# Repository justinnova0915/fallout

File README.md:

# TALOS-01 // Desktop Helper

The TALOS-01 is a desktop device designed to make navigating workspace-heavy, tiling operating systems (like Arch Linux Hyprland or macOS) more straightforward by making it physical. No more memorizing convoluted keyboard shortcuts just to move a window. This is my Fallout project for Hack Club, so I'm super excited to share it!

## Why TALOS-01?

Tiling window managers like Hyprland are great, but relying entirely on abstract keybinds can get annoying and lacks physical intuition. The goal of TALOS-01 is to turn window and workspace management into a tactile experience.

## Custom Features

- The device splits into a Main Console and a Macro Pad that snap together using strong magnet pogo pins.
- The device uses an MGN7H miniature linear rail with a button on it to let you grab and slide windows across active workspaces.
- Dedicated DMG19480T088_01WN screen displays useful widgets (time, weather, Discord call status) to free up your main monitor real estate entirely for games or code.
- A custom 3x3 macro pad module for standard macro inputs.
- A physical 5V analog needle voltmeter to display real-time metrics like CPU usage or core temperatures.
- Powerful ESP32 Controller for the brain of the device. Communicates with your PC over Bluetooth.
- Supports wireless power using two internal 18650 batteries, or wired over USB-C.

## Device Design

The TALOS-01 design is heavily inspired by the design language of *Arknights: Endfield*. The entire body uses a matching color palette of black, grey, white, and yellow, detailed with topographic lines and techy text accents.

> Disclaimer: This project is a non-commercial, fan-made creation featuring visual and UI assets inspired by *Arknights: Endfield*, which remain the intellectual property of **Hypergryph**.

* **PCB and circuitry:**
It's built around a custom parent PCB that hosts every single chip. The board has exposed headers to connect to the moving slider handle and the macro pad (excuse any messy routing) ;).  
To power it, you can plug in USB-C to feed the TP4056 charging circuit, or let it run completely wireless off the 18650 batteries. Power leaving the circuit is stepped up using two independent MT3608 boost converters (a 12V line for the smart display and a 5V line for the ESP32 and voltmeter), before hitting an AMS1117-3.3 linear regulator for the shared sensor bus.

* **The Slider & Encoder:** The custom 3D-printed handle rides on the MGN7H rail and holds a DRV2605 driver with a motor to deliver physical haptic feedback clicks as you pass items. Distance tracking is calculated using two SS49E hall effect sensors positioned exactly a quarter turn from each other on the bottom of the block. All sensors and drivers tucked inside the moving handle connect back to the parent PCB via a Flat Flexible Cable (FFC).

* **Macro Pad:** To avoid a massive, fragile bundle of wires across the split-enclosure gap, I put a PCF8574 IO expander to condense the 3x3 matrix, gauge, and power button down into a simple 4-line I2C bus, meaning the whole wing connection only needs 7 physical pogo pins to bridge the gap! The analog needle gauge runs on a 5V scale, but the ESP32 can only natively supply a 3.3V logic signal. I put together a simple 2N3094 transistor circuit to shift the downstream signal up cleanly to the required 5V.

## Firmware and Software
The screen graphics are built and flashed to the hardware independently using DWIN's native configuration environment and software utility tools. This allows the smart display to handle its own graphics processing over an 8-pin connection to the ESP32. This stops the ESP32 from lagging out under heavy rendering, so it can focus purely on passing lightweight UI control commands over UART!

On the desktop side, a custom-written daemon in GOLANG runs continuously to translate signals coming from the ESP32 over Bluetooth and send information to the device.

## How to Build and Use

#### 1. Hardware Assembly
1. **PCB:** Get the board fabricated using the gerbers files inside `Fallout_PCB`.
2. **Components:** Grab all components listed in the [BOM](https://github.com/justinnova0915/fallout/blob/main/BOM.csv).
3. **3D Printing & Assembly:** Print the housing from `Fallout_CAD`, and assemble according to the 3d model.
4. **Wiring Diagram**  
  
Wiring diagram for the main board  
  
Macro Pad Wiring Diagram
#### 2. Flashing Firmware
- **Smart Display:** The screen graphics are built and flashed to the hardware independently using DWIN's native configuration environment and software utility tools call DGUS. Simply follow their Bilibili tutorial.
- **ESP32 Core:** Open the `Fallout_Software/Firmware` project in your environment, then build and flash using vscode's esp-idf tool.

#### 3. Desktop Software Setup
The desktop side uses a custom daemon written in `GO` that runs continuously to catch Bluetooth strings from the ESP32 and talk to your window manager.
1. Move into the daemon directory:
    ```bash
    cd Fallout_Software/Daemon
    ```
2. Build the binary:
    ```bash
    go build main.go
    ```
3. Boot it on startup by adding it to your `hyprland.conf`:
    ```ini
    exec-once = /path/to/talos-daemon
    ```

## Resources

#### BOM
I got most of my components in person in China, but I have found equivalents for around the same price on Taobao, so that is what my BOM is going to be based off of.

You can get the BOM [here](https://github.com/justinnova0915/fallout/blob/main/BOM.xlsx).

#### CAD
The CAD files are under [`Fallout_CAD`](https://github.com/justinnova0915/fallout/tree/main/Fallout_CAD). I designed it in Fusion so you can find the f3d and stp files there.

#### PCB
> Since I was using the breakout or module versions of most ICs (it's my first PCB!), I had to make custom symbol and footprints for them.

The KiCAD source files are under [`Fallout_PCB`](https://github.com/justinnova0915/fallout/tree/main/Fallout_PCB)

#### Code
The ESP32 code is written in `C++` using `ESP-IDF`, and the Hyprland Daemon is written in `GO`.

The Code is under [`Fallout_Software`](https://github.com/justinnova0915/fallout/tree/main/Fallout_Software)

## Credits

Thanks so much to the folks on Discord and Reddit for reviewing and helping me refine the electronics! Thanks also to Hack Club for running the Fallout event which sponsored this hardware build!

## License

This project is licensed under `GNU GPLv3`.

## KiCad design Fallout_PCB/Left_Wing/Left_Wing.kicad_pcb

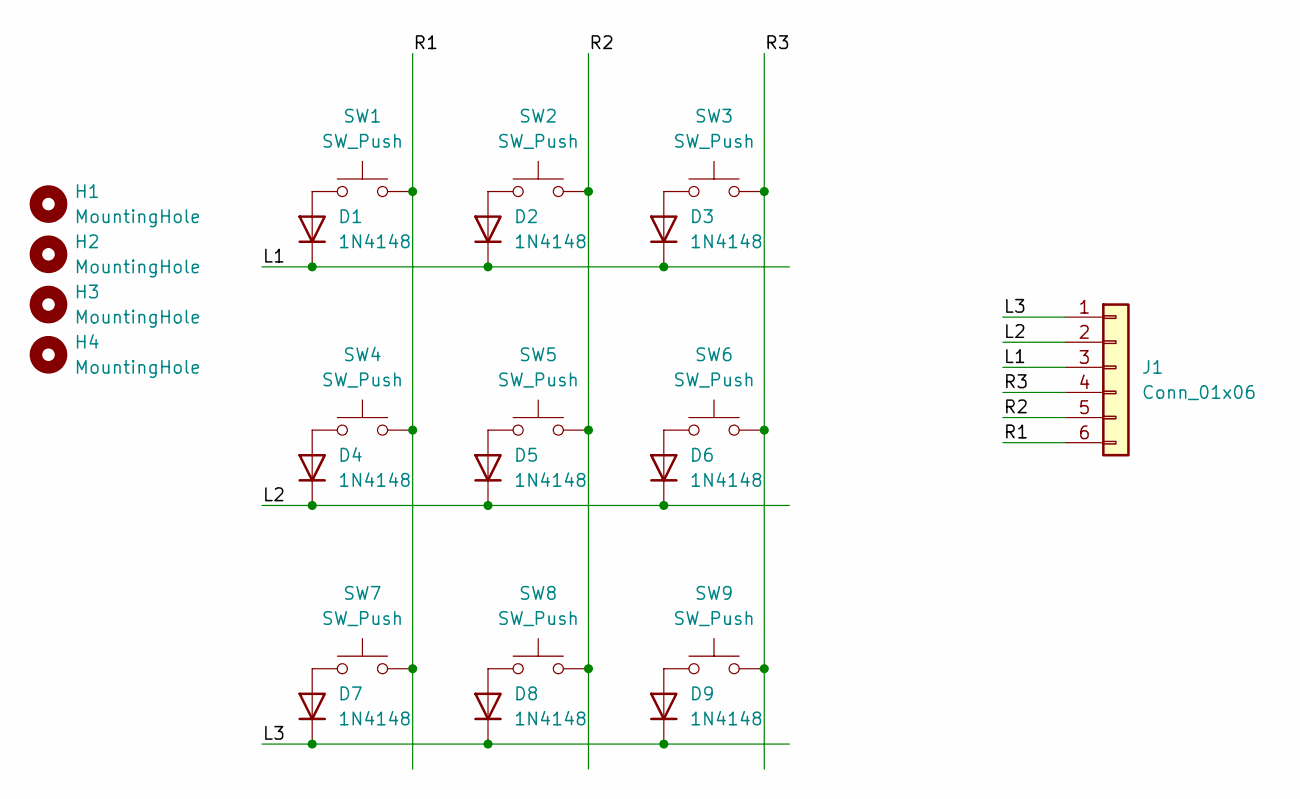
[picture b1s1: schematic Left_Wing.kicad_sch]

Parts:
D1, D2, D3, D4, D5, D6, D7, D8, D9: 1N4148; Nexperia_CFP3_SOD-123W
H1, H2, H3, H4: MountingHole; MountingHole_2mm
J1: Conn_01x06; PinHeader_1x06_P2.54mm_Vertical
SW1, SW2, SW3, SW4, SW5, SW6, SW7, SW8, SW9: SW_Push; SW_Cherry_MX_1.00u_Plate

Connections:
/L1: D1.1 (K), D2.1 (K), D3.1 (K), J1.3
/L2: D4.1 (K), D5.1 (K), D6.1 (K), J1.2
/L3: D7.1 (K), D8.1 (K), D9.1 (K), J1.1
/R1: J1.6, SW1.2, SW4.2, SW7.2
/R2: J1.5, SW2.2, SW5.2, SW8.2
/R3: J1.4, SW3.2, SW6.2, SW9.2
unnamed: D1.2 (A), SW1.1
unnamed: D2.2 (A), SW2.1
unnamed: D3.2 (A), SW3.1
unnamed: D4.2 (A), SW4.1
unnamed: D5.2 (A), SW5.1
unnamed: D6.2 (A), SW6.1
unnamed: D7.2 (A), SW7.1
unnamed: D8.2 (A), SW8.1
unnamed: D9.2 (A), SW9.1

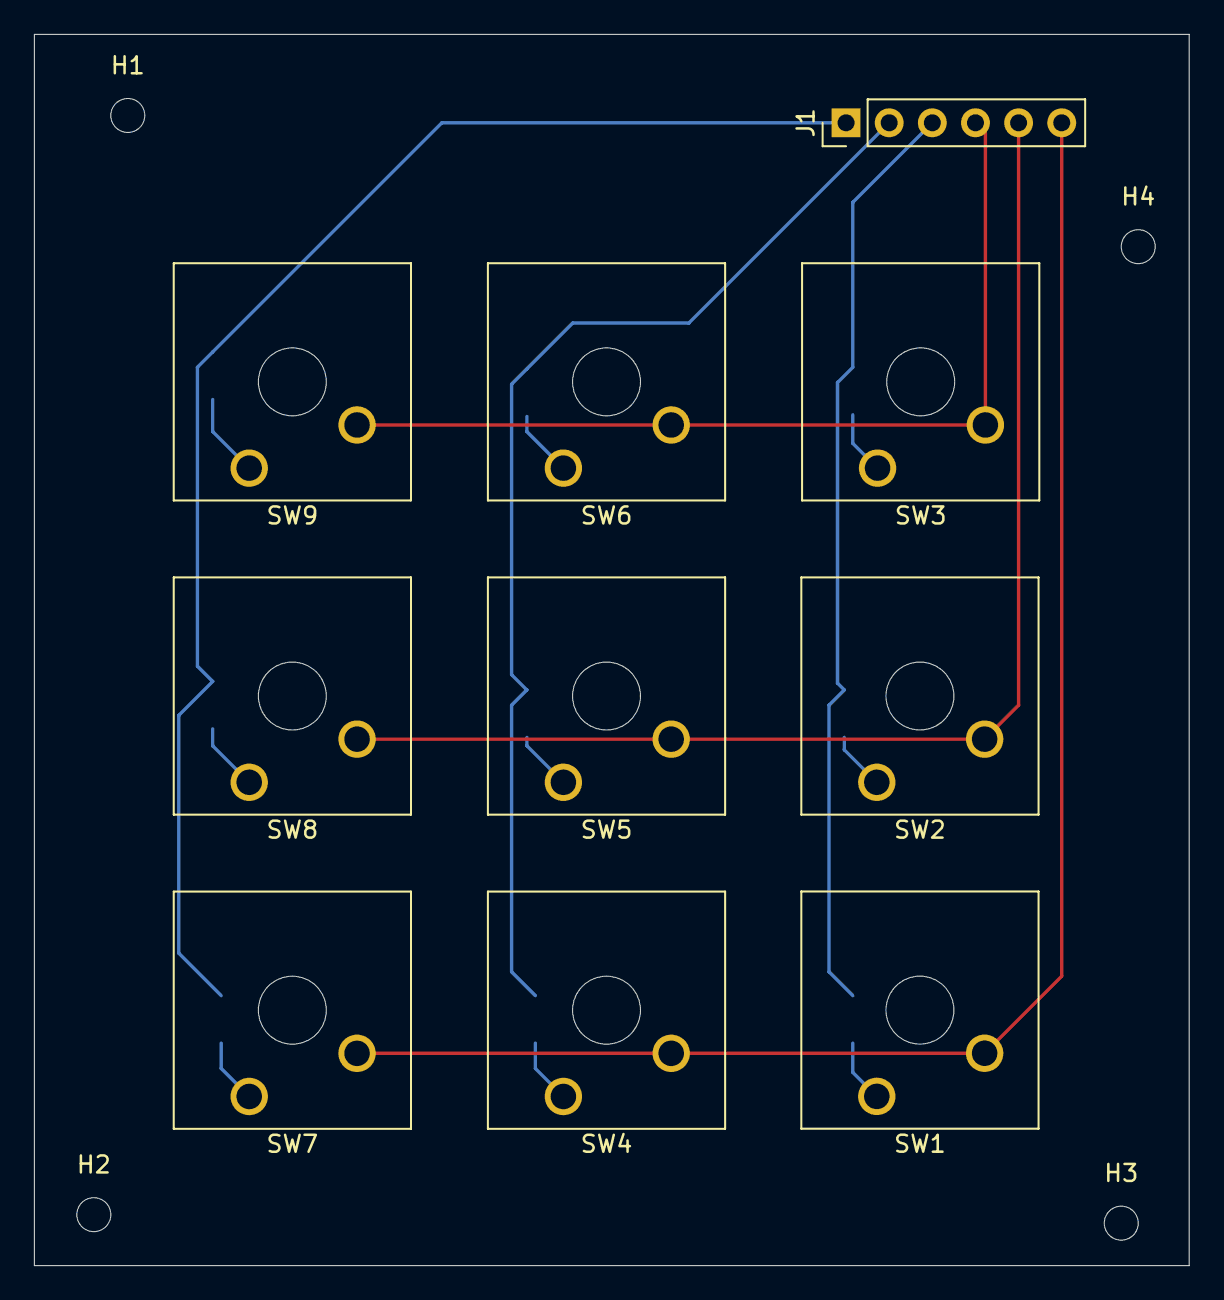
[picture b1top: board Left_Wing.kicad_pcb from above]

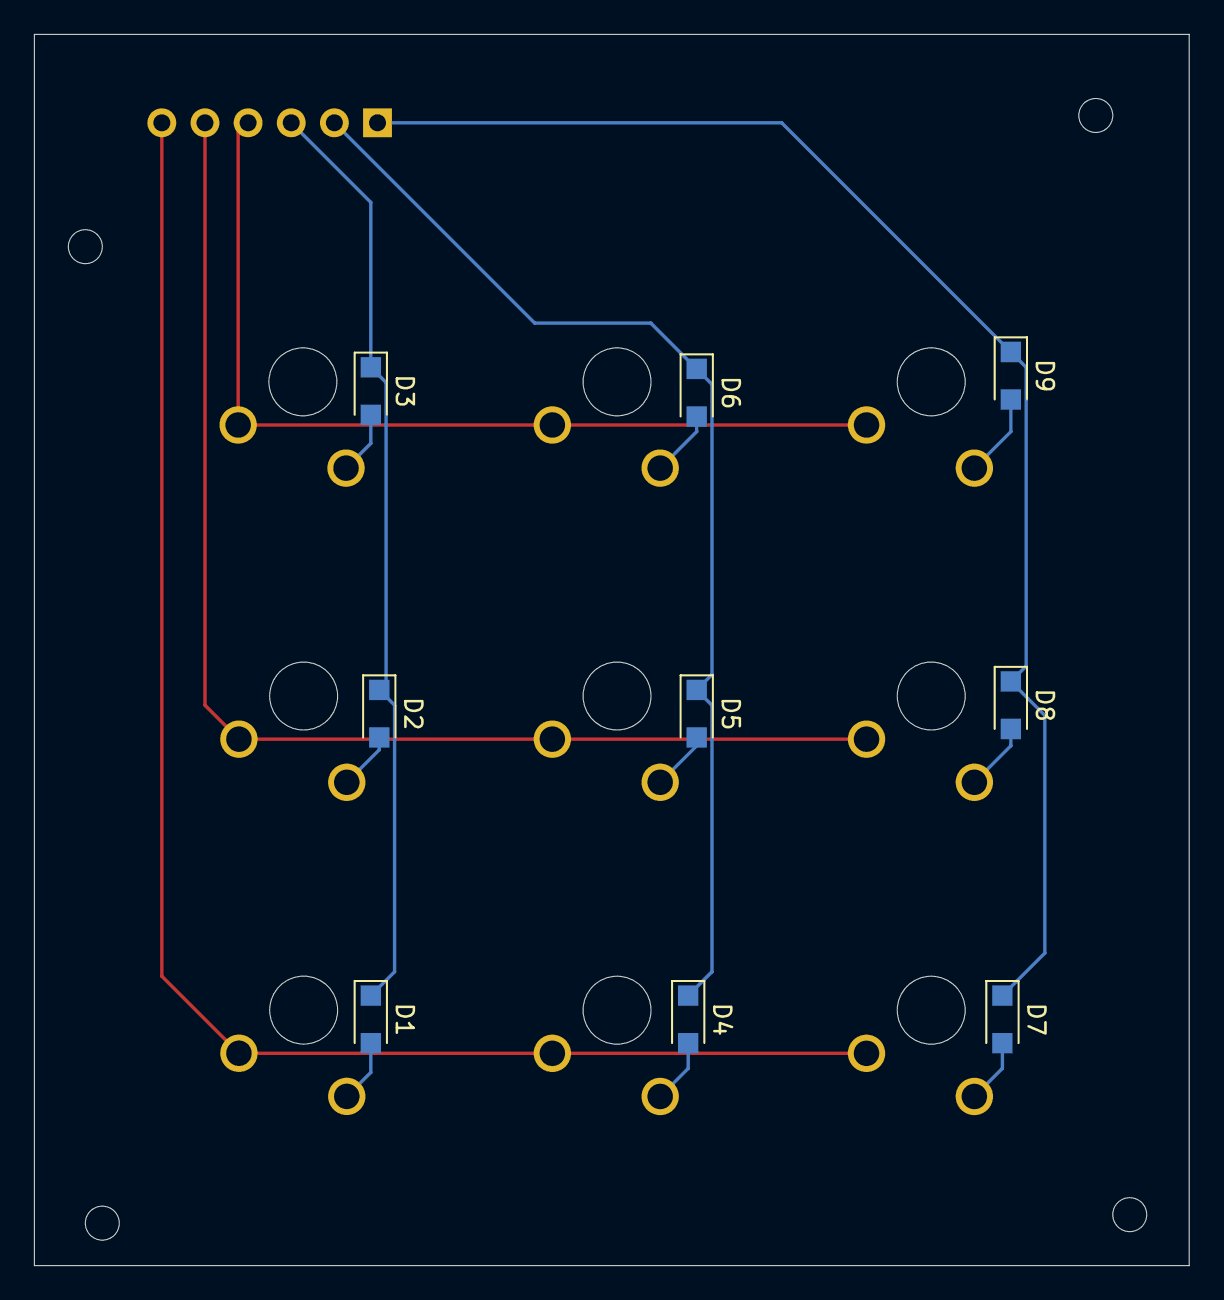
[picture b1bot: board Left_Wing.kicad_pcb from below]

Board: 2 copper layers, 68.0 x 72.5 mm, 23 parts (9 on the bottom side), 15 nets.

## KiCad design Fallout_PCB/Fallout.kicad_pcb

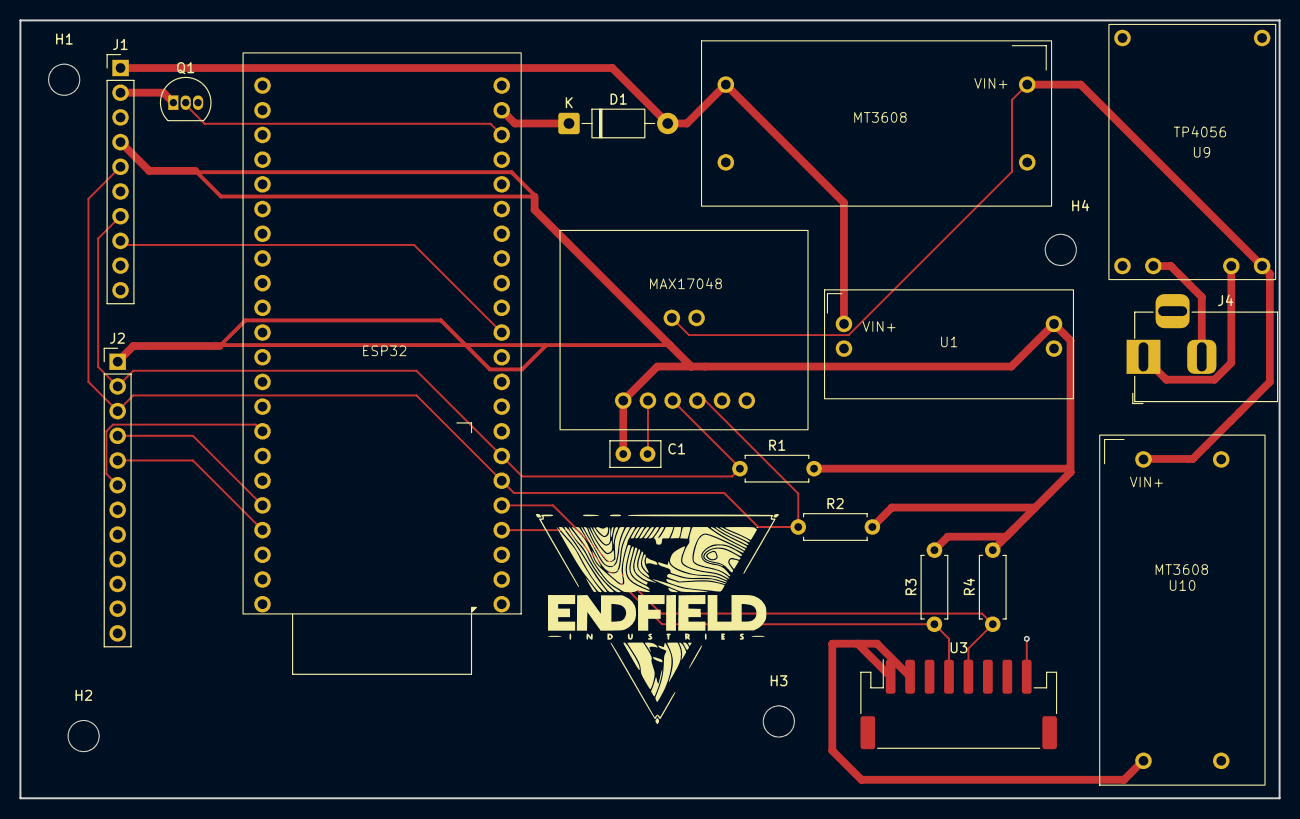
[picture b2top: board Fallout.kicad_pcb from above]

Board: 2 copper layers, 129.5 x 80.0 mm, 21 parts (0 on the bottom side), 18 nets.

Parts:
C1: C; C_Disc_D5.0mm_W2.5mm_P2.50mm
D1: 1N5819; D_DO-41_SOD81_P10.16mm_Horizontal
H1, H2, H3, H4: MountingHole; MountingHole_3.2mm_M3
J1: Conn_01x10; PinHeader_1x10_P2.54mm_Vertical
J2: Conn_01x12; PinHeader_1x12_P2.54mm_Vertical
J4: Barrel_Jack; BarrelJack_Horizontal
Q1: 2N3904; TO-92_Inline
R1, R2, R3, R4: R; R_Axial_DIN0207_L6.3mm_D2.5mm_P7.62mm_Horizontal
U1: AMS1117-3.3
U2, U10: MT3608
U3: DWIN19480C088_03WN; JST_PH_S8B-PH-SM4-TB_1x08-1MP_P2.00mm_Horizontal
U4: ESP32-S3-WROOM-1; ESP32_Module
U6: MAX17048
U9: TP4056

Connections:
/5V+: D1.2 (A), J1.1, U1.3 (VI), U2.3 (VOUT+)
/AMS1117_3.3: C1.1, J1.4, J2.1, R1.2, R2.2, R3.2, R4.2, U1.2 (VO), U6.1 (VIN)
/B+: J4.1, U9.5 (B+)
/B-: J4.2, U9.6 (B-)
/DWIN+: U3.1 (VIN), U3.2 (VIN), U10.3 (VOUT+)
/ESP32_INT: J1.8, U4.12 (IO8)
/ESP32_RX: R4.1, U3.5 (TX2), U4.5 (IO5)
/ESP32_SCL: J1.7, J2.2, R1.1, U4.7 (IO7), U6.3 (SCL)
/ESP32_SDA: J1.5, J2.3, R2.1, U4.6 (IO6), U6.4 (SDA)
/ESP32_SS1: J2.4, U4.38 (IO2)
/ESP32_SS2: J2.5, U4.39 (IO1)
/ESP32_SW: J2.6, U4.33 (IO40)
/ESP32_TX: R3.1, U3.4 (RX2), U4.4 (IO4)
/ESP_5V+: D1.1 (K), U4.5Vin (5VIN)
/TP4056+: U2.1 (VIN+), U6.7 (JST+), U9.3 (OUT+), U10.1 (VIN+)
/Voltmeter-: J1.2, Q1.1 (E)
/Voltmeter_Base: Q1.2 (B), U4.22 (IO14)
GND: C1.2, J1.9, J2.12, Q1.3 (C), U1.1 (GND), U2.2 (VIN-), U2.4 (VOUT-), U3.8 (GND), U4.1 (GND), U6.2 (GND), U6.6 (QStart), U6.8 (JST-), U9.4 (OUT-), U10.2 (VIN-), U10.4 (VOUT-)

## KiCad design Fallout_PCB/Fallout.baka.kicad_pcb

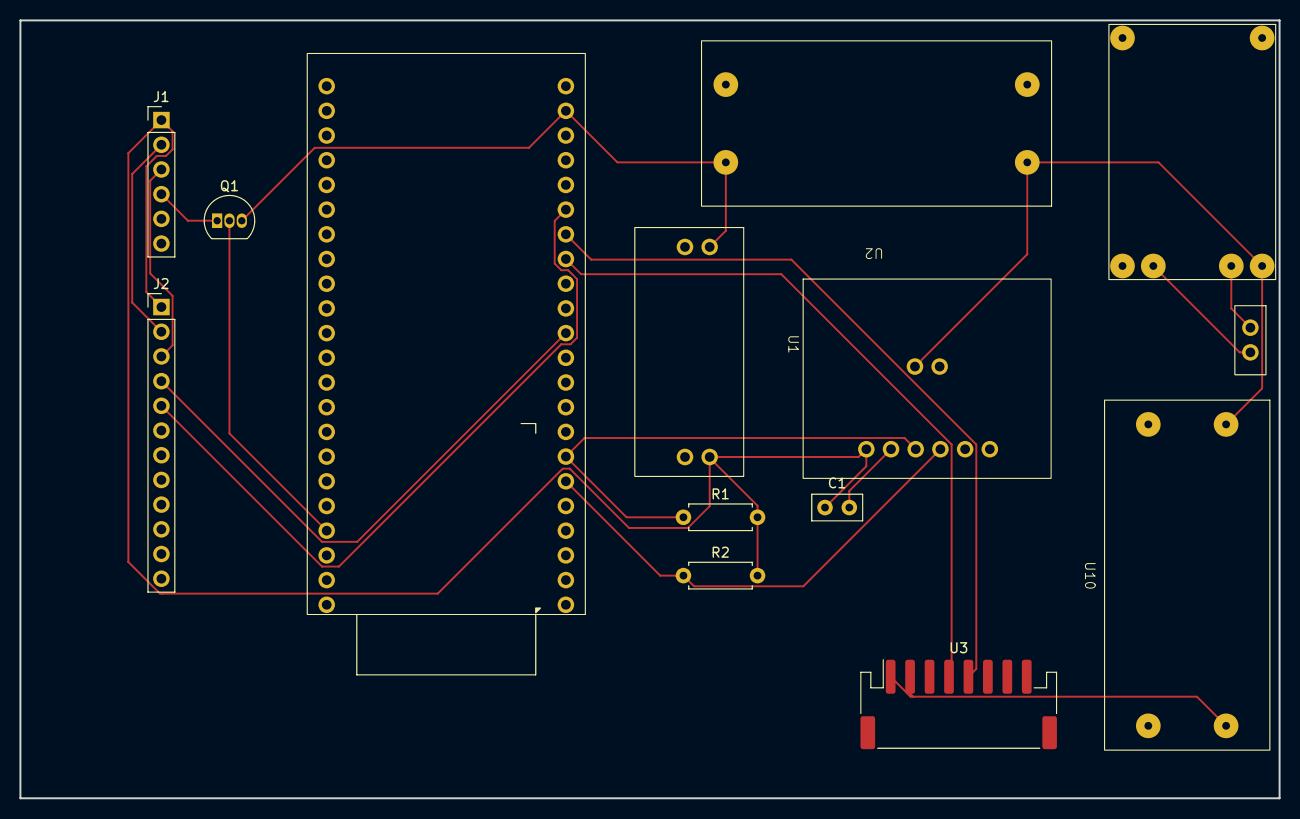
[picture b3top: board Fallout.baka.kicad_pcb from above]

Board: 2 copper layers, 129.5 x 80.0 mm, 14 parts (0 on the bottom side), 15 nets.

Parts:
C1: C; C_Disc_D5.0mm_W2.5mm_P2.50mm
J1: Conn_01x06; PinHeader_1x06_P2.54mm_Vertical
J2: Conn_01x12; PinHeader_1x12_P2.54mm_Vertical
J3: Batt_Connector; Bat_Connector
Q1: 2N3904; TO-92_Inline
R1, R2: R; R_Axial_DIN0207_L6.3mm_D2.5mm_P7.62mm_Horizontal
U1: AMS1117-3.3
U2, U10: MT3608
U3: DWIN19480C088_03WN; JST_PH_S8B-PH-SM4-TB_1x08-1MP_P2.00mm_Horizontal
U4: ESP32-S3-WROOM-1; ESP32_Module
U6: MAX17048
U9: TP4056

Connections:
/5V+: Q1.3 (C), U1.3 (VI), U2.3 (VOUT+), U4.5Vin (5VIN)
/AMS1117_3.3: C1.1, J1.1, J2.1, R1.2, R2.2, U1.2 (VO), U6.1 (VIN)
/DWIN+: U3.1 (VIN), U3.2 (VIN), U10.3 (VOUT+)
/ESP32_PWM: J2.4, U4.12 (IO8)
/ESP32_RX: U3.5 (TX2), U4.18 (IO10)
/ESP32_SCL: J1.2, J2.2, R1.1, U4.7 (IO7), U6.3 (SCL)
/ESP32_SDA: J1.3, J2.3, R2.1, U4.6 (IO6), U6.4 (SDA)
/ESP32_SW: J2.5, U4.19 (IO11)
/ESP32_TX: U3.4 (RX2), U4.17 (IO9)
/TP4056+: U2.1 (VIN+), U6.7 (JST+), U9.3 (OUT+), U10.1 (VIN+)
/Voltmeter+: J1.4, Q1.1 (E)
GND: C1.2, J1.5, U1.1 (GND), U2.2 (VIN-), U2.4 (VOUT-), U3.8 (GND), U4.1 (GND), U6.2 (GND), U6.8 (JST-), U9.4 (OUT-), U10.2 (VIN-), U10.4 (VOUT-)
unnamed: J3.1, U9.5 (B+)
unnamed: J3.2, U9.6 (B-)
unnamed: Q1.2 (B), U4.39 (IO1)

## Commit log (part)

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2026-06-06 Fixed Readme.md duplicated file ending
2026-06-06 Fixed Firmware Nested Repo
2026-06-06 Added Zine to readme
2026-06-06 Added BOM
2026-06-06 Refined readme
2026-06-06 Fixed File Format, and using Git LFS
2026-06-06 Gerbers, Markdown, and Go files
2026-06-06 Fixes
2026-06-07 Enhancement
2026-06-07 Cleaned up Repository
2026-06-10 Updated BOM with English version
2026-06-10 stash
2026-06-10 Updated BOM with English Ver.
2026-06-10 Changed BOM format to UTF-8 CSV
2026-06-17 Working Somewhat
2026-06-18 "Maybe that means he's into little girls"
